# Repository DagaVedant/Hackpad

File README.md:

# minipad

a 3x3 macropad for shortcuts, built for [hackpad](https://hackpad.hackclub.com).
9 keys, a rotary encoder, per key rgb, and a 0.91" oled that shows a clock and a
spinning globe.

## the pad

rendered from the actual case and board files in this repo, not a mockup. photo
of the real thing goes here once it's printed and soldered.

## schematic

## pcb

96.38 x 90.90mm, 2 layers. chamfered corners, and 4x m3 mounting holes on an
88.226 x 82.748mm rectangle for a sandwich case.

the 9 sk6812mini-e leds are reverse mounted. they sit in milled slots in the
board and shine up through the switches, so the lighting is per key rather than
underglow.

## case

[open the assembly in onshape](https://cad.onshape.com/documents/58a01ca66c97d1b4010a7a00/w/fc5b38729478e50a03cca7d8/e/0de70a1a8ca9505f551d6dfe?renderMode=0&uiState=6a9506f6d62aea1f59718b50)

a sandwich: 1.5mm switch plate on top, the pcb in the middle, tray bottom
underneath. 102.38 x 96.90mm overall, 16.6mm tall closed.

the pcb rests on four bosses at 10mm, which leaves a 7.5mm cavity under the
board for the reverse mounted leds and the xiao. m3 heatset inserts drop into
the bosses from above, and four m3 screws through the plate into those inserts
hold the stack together. the only overhang is the usb-c slot in the side wall,
which is a 7mm bridge.

`production/Top.STEP` and `production/Bottom.STEP` are the two printable parts.
`cad/Assembly.STEP` is the whole thing put together, with the pcb in it.

## oled

the globe is generated from real natural earth coastline data. 24 frames, made
by projecting the land polygons onto a tilted sphere, so those are actual
continents at 32x32 pixels.

## bom

| qty | part | refs | in the hackpad kit? |
|---|---|---|---|
| 1 | seeed xiao rp2040 | U1 | yes (1 supplied) |
| 9 | mx style switch | SW1-SW9 | yes (16 supplied) |
| 9 | 1n4148 diode, do-35 | D10-D18 | yes (20 supplied) |
| 9 | sk6812mini-e rgb led | D1-D9 | yes (20 supplied) |
| 1 | ec11 rotary encoder, 20mm d-shaft | SW10 | yes (2 supplied) |
| 1 | 0.91" 128x32 i2c oled | U2 | yes (1 supplied) |
| 9 | dsa blank keycap | - | yes (16 supplied) |
| 4 | m3x16 screw | H1-H4 | yes (6 supplied) |
| 4 | m3x5x4 heatset insert | H1-H4 | yes (6 supplied) |
| 1 | knob for the encoder | - | **no, print it or source it yourself** |

everything except the encoder knob comes from the standard kit.

## keymap

| | | |
|---|---|---|
| open spotify | open chrome | open vs code |
| f11 | screenshot | calculator |
| copy | paste | undo |

the encoder does volume.

the three app launchers use windows taskbar shortcuts (`win`+`1`/`2`/`3`), so
**pin spotify, chrome and vs code to the first three taskbar slots** and the top
row works with no extra software.

## clock

there's no rtc on the board and usb hid can't send the time, so the clock
free runs from a timer and you set it by hand:

- hold the two **top corner keys** together to toggle set mode
- **encoder** adjusts minutes
- **top left / top right** keys adjust hours
- **top middle** exits

it resets to 00:00:00 whenever you unplug it, and drifts a few seconds a day.

## pins

| xiao pin | rp2040 | function |
|---|---|---|
| d0, d1, d2 | gp26, gp27, gp28 | matrix columns |
| d3, d7, d10 | gp29, gp1, gp3 | matrix rows |
| d4, d5 | gp6, gp7 | oled i2c (sda, scl) |
| d6 | gp0 | sk6812 data |
| d8, d9 | gp2, gp4 | encoder b, a |

3x3 matrix, `row2col`. all 11 gpio are used, which is why the encoder's push
switch isn't wired.

## firmware

qmk. `production/firmware.uf2` is prebuilt, so to flash it just double tap reset
on the xiao and drag the file onto the drive that appears.

to build it yourself, drop `firmware/` into
`qmk_firmware/keyboards/minipad/` and run:

```
qmk compile -kb minipad -km default
```

## layout

```
pcb/         kicad source and the board step
firmware/    qmk source
cad/         assembled case model
production/  everything you need to build one: gerbers, the two
             printable case parts, and the prebuilt uf2
assets/      images for this readme
```

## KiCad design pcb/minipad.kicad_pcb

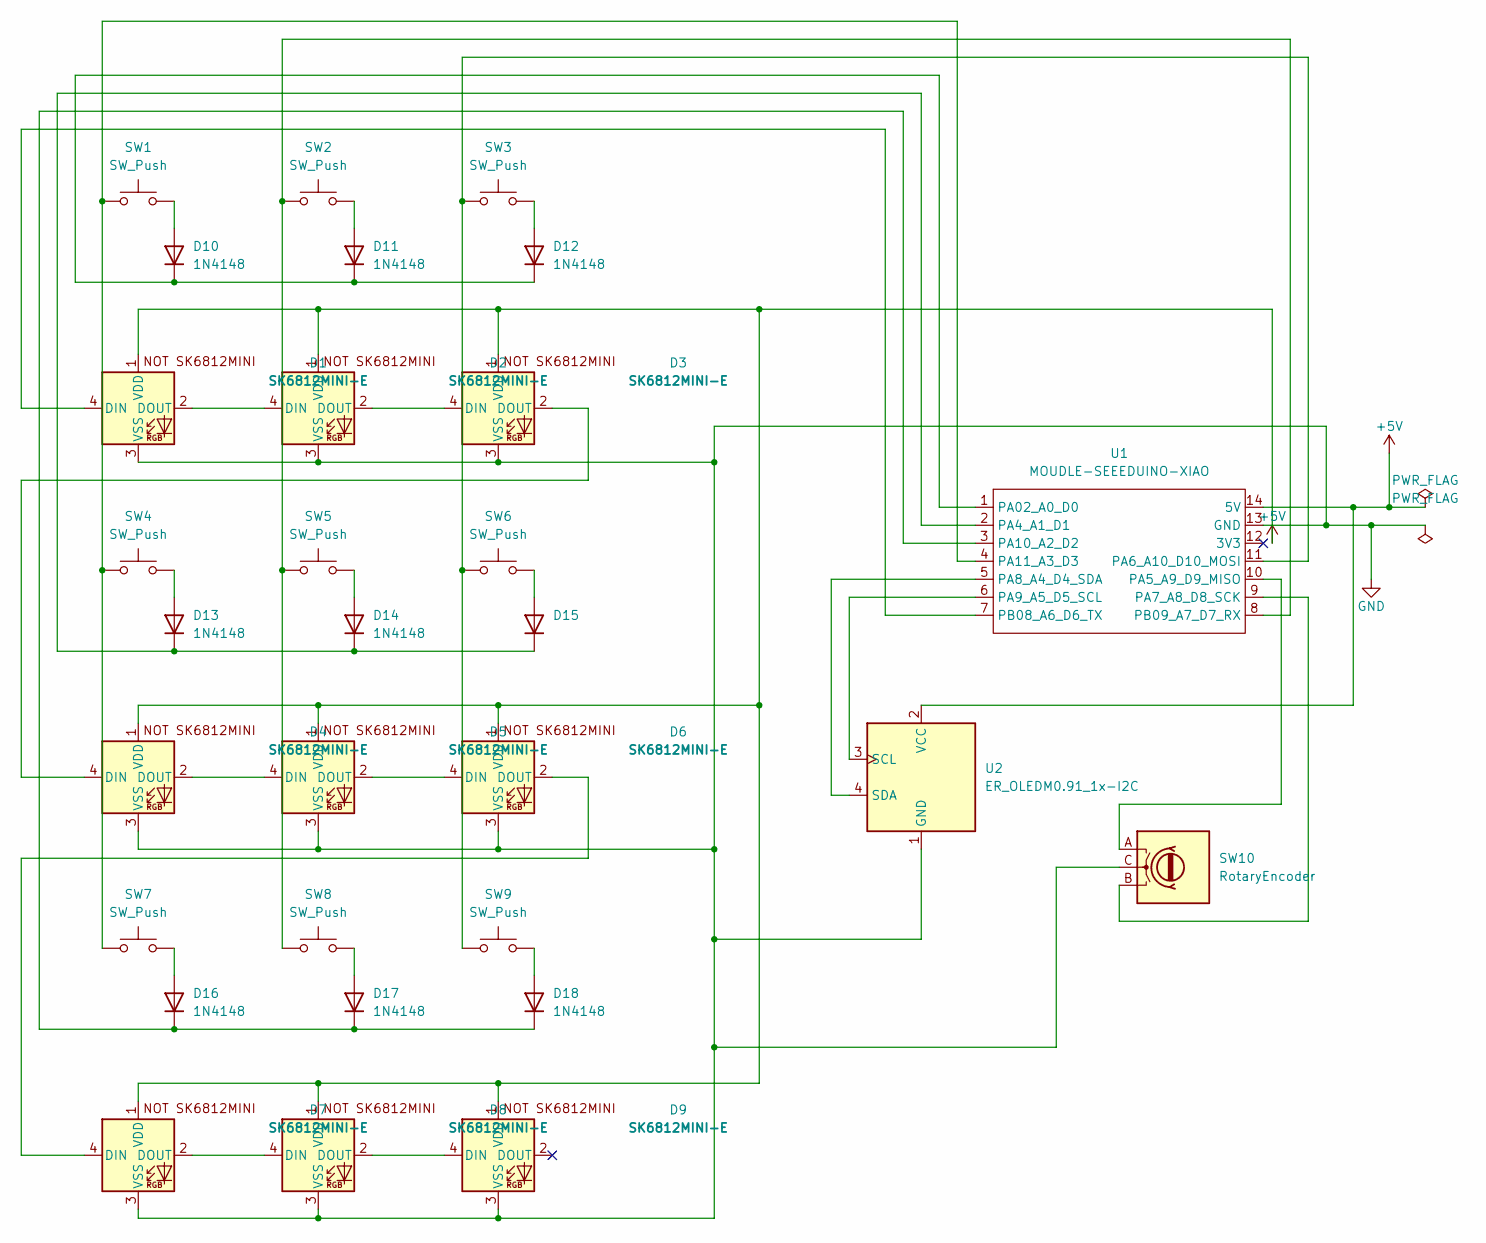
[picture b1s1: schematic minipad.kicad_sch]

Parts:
D1, D2, D3, D4, D5, D6, D7, D8, D9: SK6812MINI-E; SK6812MINI-E_fixed
D10, D11, D12, D13, D14, D15, D16, D17, D18: 1N4148; D_DO-35_SOD27_P7.62mm_Horizontal
SW1, SW2, SW3, SW4, SW5, SW6, SW7, SW8, SW9: SW_Push; SW_Cherry_MX_1.00u_PCB
SW10: RotaryEncoder; RotaryEncoder_Alps_EC11E-Switch_Vertical_H20mm
U1: MOUDLE-SEEEDUINO-XIAO; XIAO-Generic-Hybrid-14P-2.54-21X17.8MM
U2: ER_OLEDM0.91_1x-I2C

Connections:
+5V: D1.1 (VDD), D2.1 (VDD), D3.1 (VDD), D4.1 (VDD), D5.1 (VDD), D6.1 (VDD), D7.1 (VDD), D8.1 (VDD), D9.1 (VDD), U1.14 (5V), U2.2 (VCC)
GND: D1.3 (VSS), D2.3 (VSS), D3.3 (VSS), D4.3 (VSS), D5.3 (VSS), D6.3 (VSS), D7.3 (VSS), D8.3 (VSS), D9.3 (VSS), SW10.C, U1.13 (GND), U2.1 (GND)
unnamed: D1.4 (DIN), U1.7 (PB08_A6_D6_TX)
unnamed: D1.2 (DOUT), D2.4 (DIN)
unnamed: D2.2 (DOUT), D3.4 (DIN)
unnamed: D3.2 (DOUT), D4.4 (DIN)
unnamed: D4.2 (DOUT), D5.4 (DIN)
unnamed: D5.2 (DOUT), D6.4 (DIN)
unnamed: D6.2 (DOUT), D7.4 (DIN)
unnamed: D7.2 (DOUT), D8.4 (DIN)
unnamed: D8.2 (DOUT), D9.4 (DIN)
unnamed: D10.2 (A), SW1.2
unnamed: D10.1 (K), D11.1 (K), D12.1 (K), U1.1 (PA02_A0_D0)
unnamed: D11.2 (A), SW2.2
unnamed: D12.2 (A), SW3.2
unnamed: D13.2 (A), SW4.2
unnamed: D13.1 (K), D14.1 (K), D15.1 (K), U1.2 (PA4_A1_D1)
unnamed: D14.2 (A), SW5.2
unnamed: D15.2 (A), SW6.2
unnamed: D16.2 (A), SW7.2
unnamed: D16.1 (K), D17.1 (K), D18.1 (K), U1.3 (PA10_A2_D2)
unnamed: D17.2 (A), SW8.2
unnamed: D18.2 (A), SW9.2
unnamed: SW10.A, U1.10 (PA5_A9_D9_MISO)
unnamed: SW3.1, SW6.1, SW9.1, U1.11 (PA6_A10_D10_MOSI)
unnamed: SW10.B, U1.9 (PA7_A8_D8_SCK)
unnamed: U1.5 (PA8_A4_D4_SDA), U2.4 (SDA)
unnamed: U1.6 (PA9_A5_D5_SCL), U2.3 (SCL)
unnamed: SW1.1, SW4.1, SW7.1, U1.4 (PA11_A3_D3)
unnamed: SW2.1, SW5.1, SW8.1, U1.8 (PB09_A7_D7_RX)

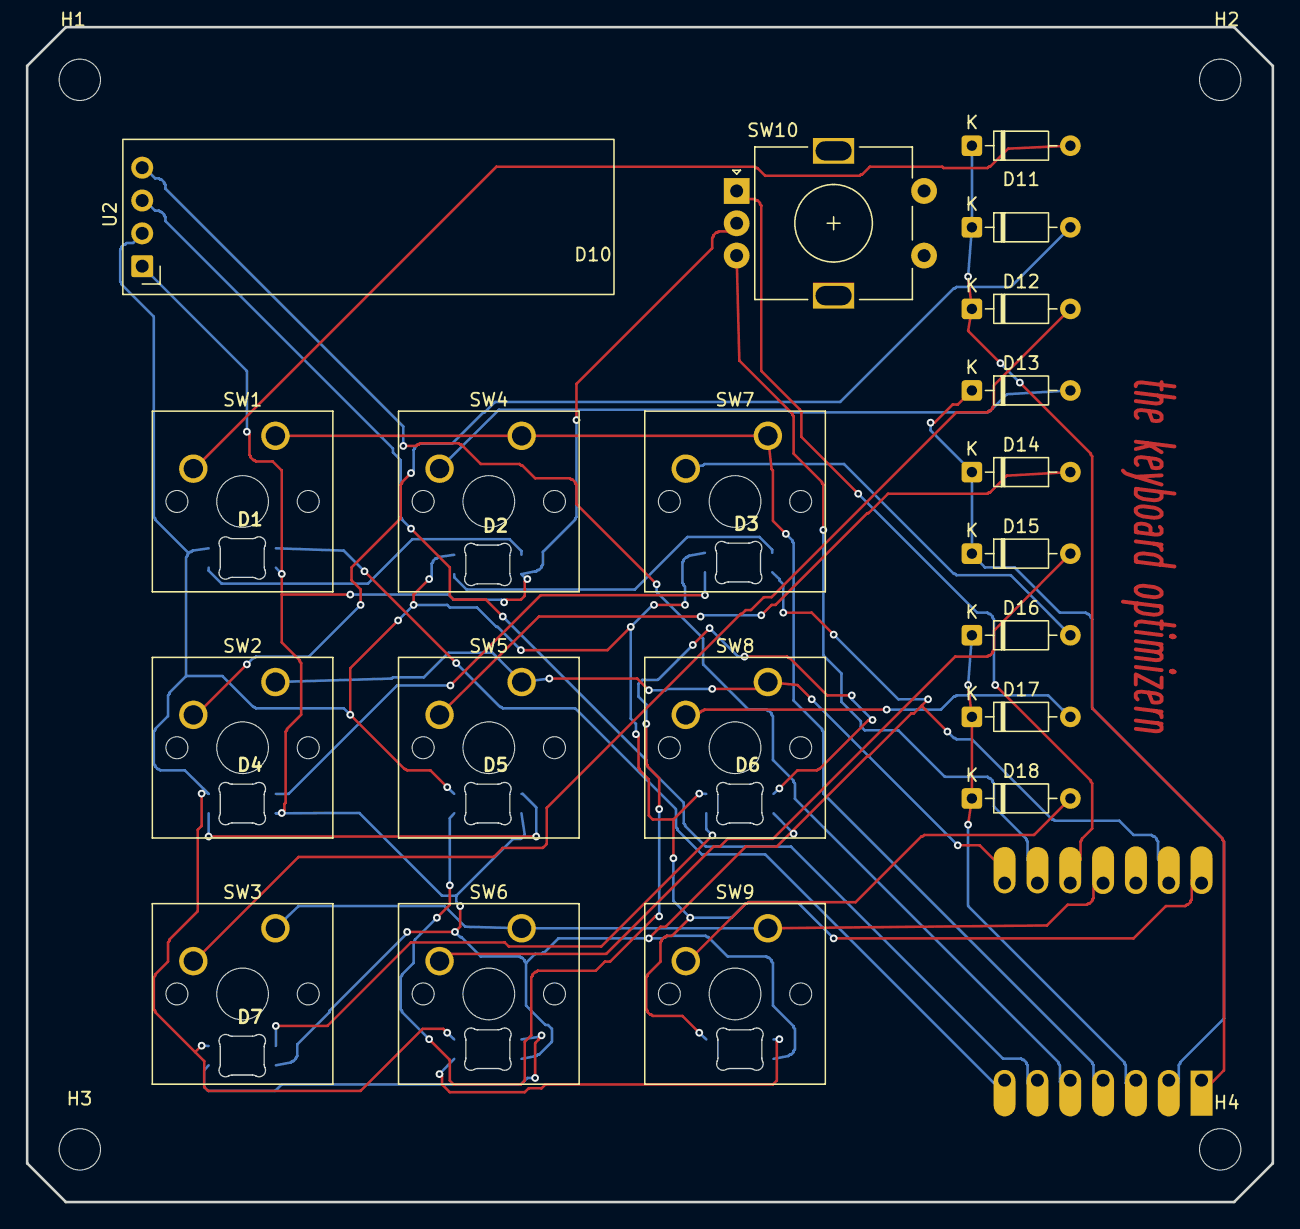
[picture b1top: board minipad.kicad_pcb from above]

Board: 2 copper layers, 96.4 x 90.9 mm, 34 parts (1 on the bottom side), 30 nets.

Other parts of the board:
H1, H2, H3, H4: MountingHole_3.2mm_M3
